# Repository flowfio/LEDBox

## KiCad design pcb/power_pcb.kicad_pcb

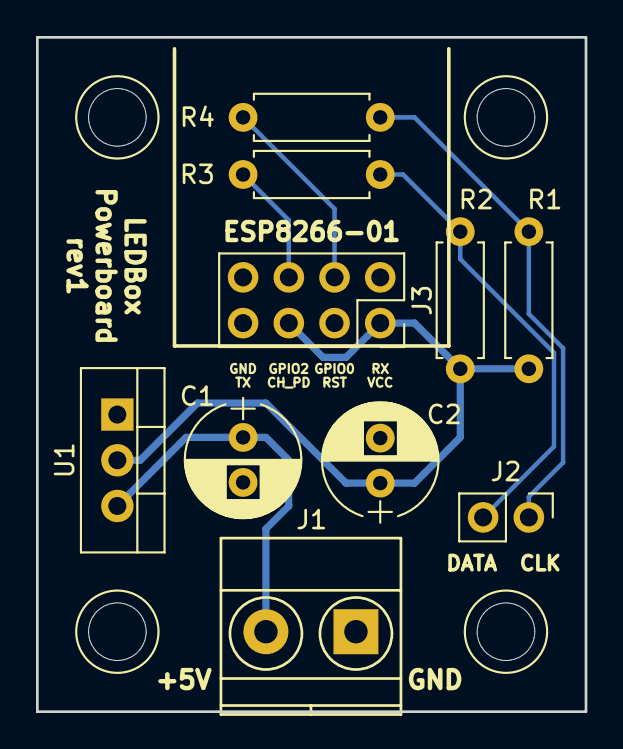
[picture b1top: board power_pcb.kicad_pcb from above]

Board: 2 copper layers, 30.5 x 37.5 mm, 10 parts (0 on the bottom side), 7 nets.

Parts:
C1: 10uF; CP_Radial_D6.3mm_P2.50mm
C2: 1uF; CP_Radial_D6.3mm_P2.50mm
J1: PWR; TerminalBlock_Pheonix_MKDS1.5-2pol
J2: IO; Pin_Header_Straight_1x02_Pitch2.54mm
J3: ESP6288-01; Socket_Strip_Straight_2x04_Pitch2.54mm
R1, R2: 3.3k; R_Axial_DIN0207_L6.3mm_D2.5mm_P7.62mm_Horizontal
R3, R4: 330; R_Axial_DIN0207_L6.3mm_D2.5mm_P7.62mm_Horizontal
U1: LD1117-3.3; TO-220_Vertical

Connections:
+3V3: C2.1, J3.1, J3.5, R1.1, R2.1, U1.2
+5V: C1.1, J1.1, U1.3
CLK: J2.1, R1.2, R3.1
DATA: J2.2, R2.2, R4.2
GND: C1.2, C2.2, J1.2, J3.8, U1.1
unnamed: J3.4, R3.2
unnamed: J3.6, R4.1

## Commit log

2017-05-30 Add files via upload
    - added basic Arduino sketch for WS2801 Artnet Client for ESP8266
2017-08-07 Power pcb v1 * Edit with KiCad * Gerber files included
2017-08-07 Fix: Added new line at EOF
